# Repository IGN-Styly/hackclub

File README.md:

# Styly's Amazing Hackpad
A simple macropad with 6 keys and an encoder knob.

[Case](https://cad.onshape.com/documents/8048d40b3579348c7bd36c3a/w/5161b2085178a2fb4e87a650/e/c5ba20084d70dba86dff4a65?renderMode=0&uiState=693449ba5ff217189cd2ce8e)
## Fearures
- 6 Keys
- 6 Leds for transparent keycaps
- 1 Encoder
# CAD Model:
Everything fits together using 4 M3 Bolts and heatset inserts.

3 Separate pieces:
- PCB
- Bottom
- Top

Made in onshape.

## PCB
Here's my PCB! It was made in KiCad.

## Firmware
This hackpad uses QMK firmware.
## BOM
- 1x XIAO RP2040
- 1x EC11 Rotary Encoder
- 6x SK6812 MINI-E LEDs
- 6x Blank DSA Keycaps
- 4x M3x16 Bolt
- 4x M3 Heatset

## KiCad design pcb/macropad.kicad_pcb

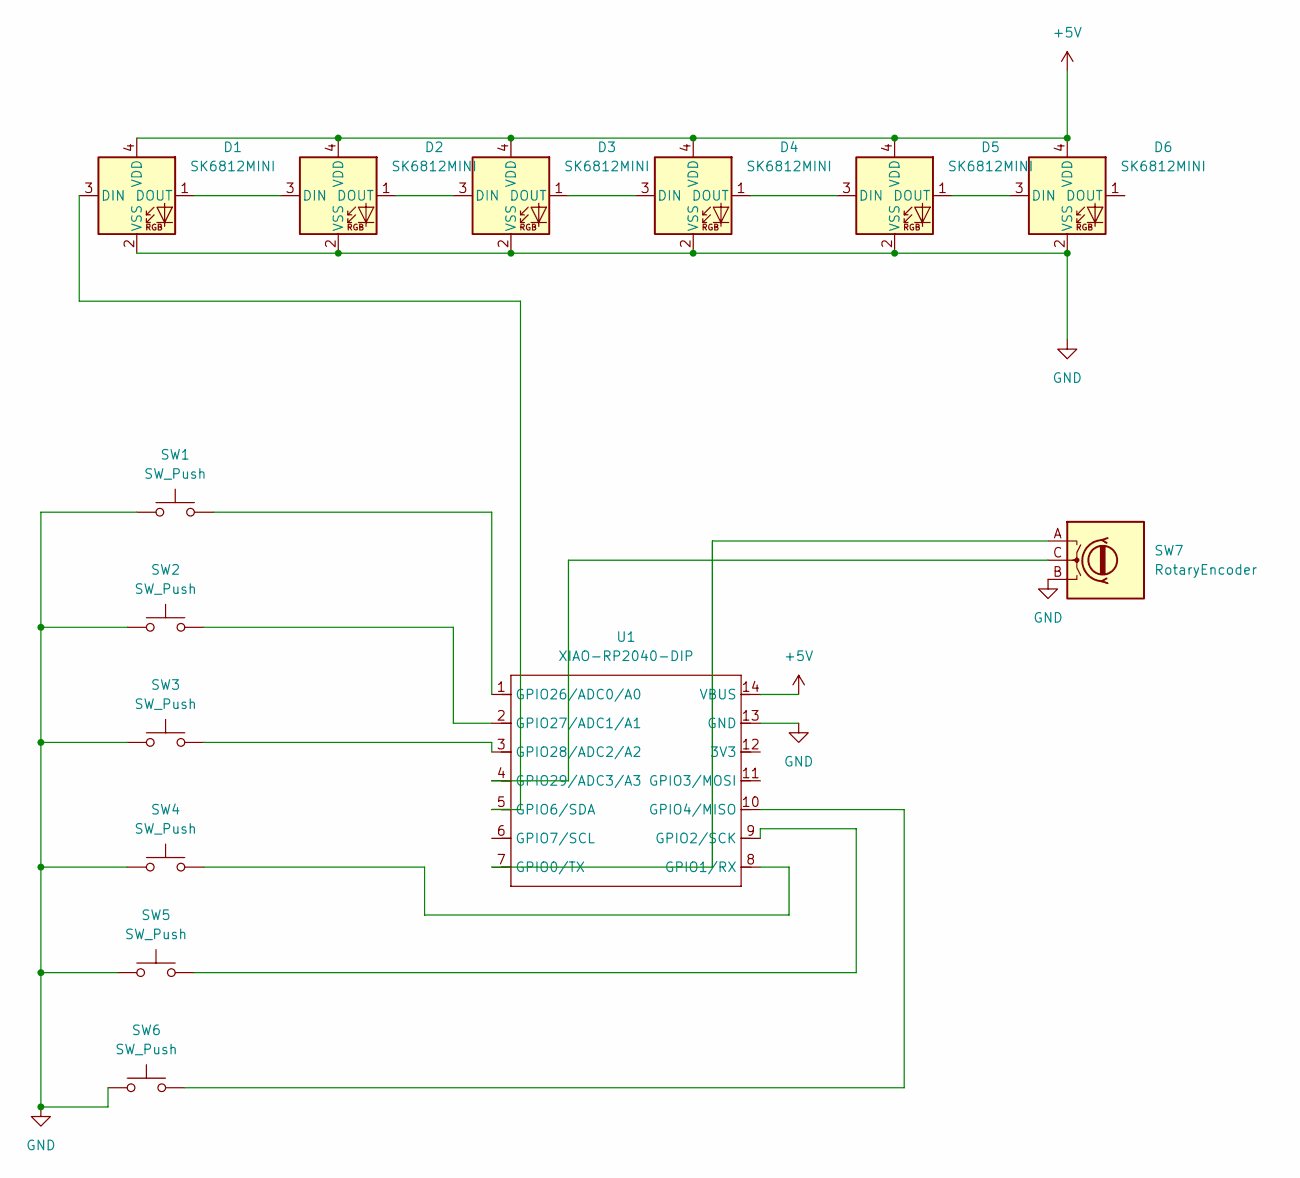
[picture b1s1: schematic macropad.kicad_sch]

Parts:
D1, D2, D3, D4, D5, D6: SK6812MINI; LED_SK6812MINI_PLCC4_3.5x3.5mm_P1.75mm
SW1, SW2, SW3, SW4, SW5, SW6: SW_Push; SW_Cherry_MX_1.00u_PCB
SW7: RotaryEncoder; RotaryEncoder_Alps_EC11E_Vertical_H20mm
U1: XIAO-RP2040-DIP

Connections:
+5V: D1.4 (VDD), D2.4 (VDD), D3.4 (VDD), D4.4 (VDD), D5.4 (VDD), D6.4 (VDD), U1.14 (VBUS)
GND: D1.2 (VSS), D2.2 (VSS), D3.2 (VSS), D4.2 (VSS), D5.2 (VSS), D6.2 (VSS), SW1.1, SW2.1, SW3.1, SW4.1, SW5.1, SW6.1, SW7.B, U1.13 (GND)
unnamed: D1.3 (DIN), U1.5 (GPIO6/SDA)
unnamed: D1.1 (DOUT), D2.3 (DIN)
unnamed: D2.1 (DOUT), D3.3 (DIN)
unnamed: D3.1 (DOUT), D4.3 (DIN)
unnamed: D4.1 (DOUT), D5.3 (DIN)
unnamed: D5.1 (DOUT), D6.3 (DIN)
unnamed: SW7.A, U1.7 (GPIO0/TX)
unnamed: SW4.2, U1.8 (GPIO1/RX)
unnamed: SW5.2, U1.9 (GPIO2/SCK)
unnamed: SW6.2, U1.10 (GPIO4/MISO)
unnamed: SW1.2, U1.1 (GPIO26/ADC0/A0)
unnamed: SW2.2, U1.2 (GPIO27/ADC1/A1)
unnamed: SW3.2, U1.3 (GPIO28/ADC2/A2)
unnamed: SW7.C, U1.4 (GPIO29/ADC3/A3)

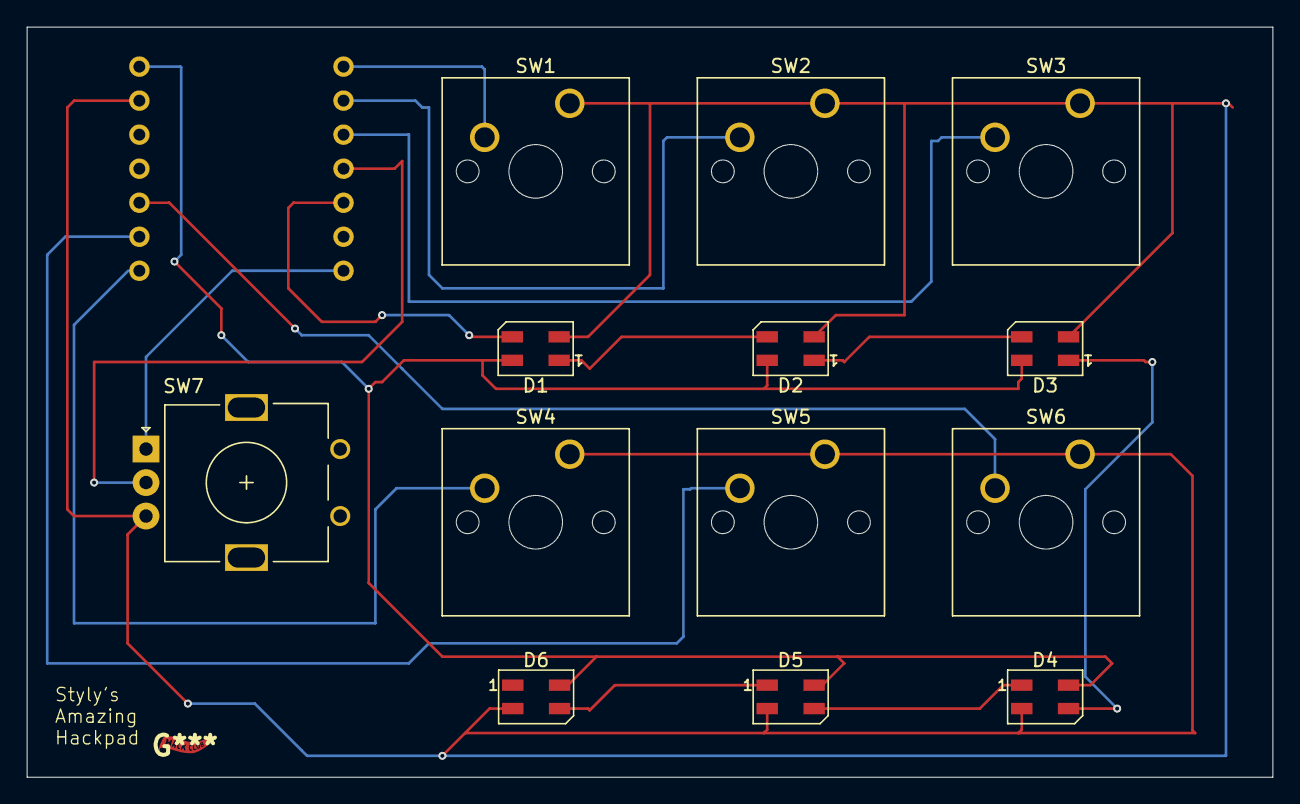
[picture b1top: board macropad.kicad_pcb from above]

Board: 2 copper layers, 93.0 x 56.0 mm, 14 parts (1 on the bottom side), 16 nets.

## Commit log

2025-12-06 init
2025-12-06 cleanup
